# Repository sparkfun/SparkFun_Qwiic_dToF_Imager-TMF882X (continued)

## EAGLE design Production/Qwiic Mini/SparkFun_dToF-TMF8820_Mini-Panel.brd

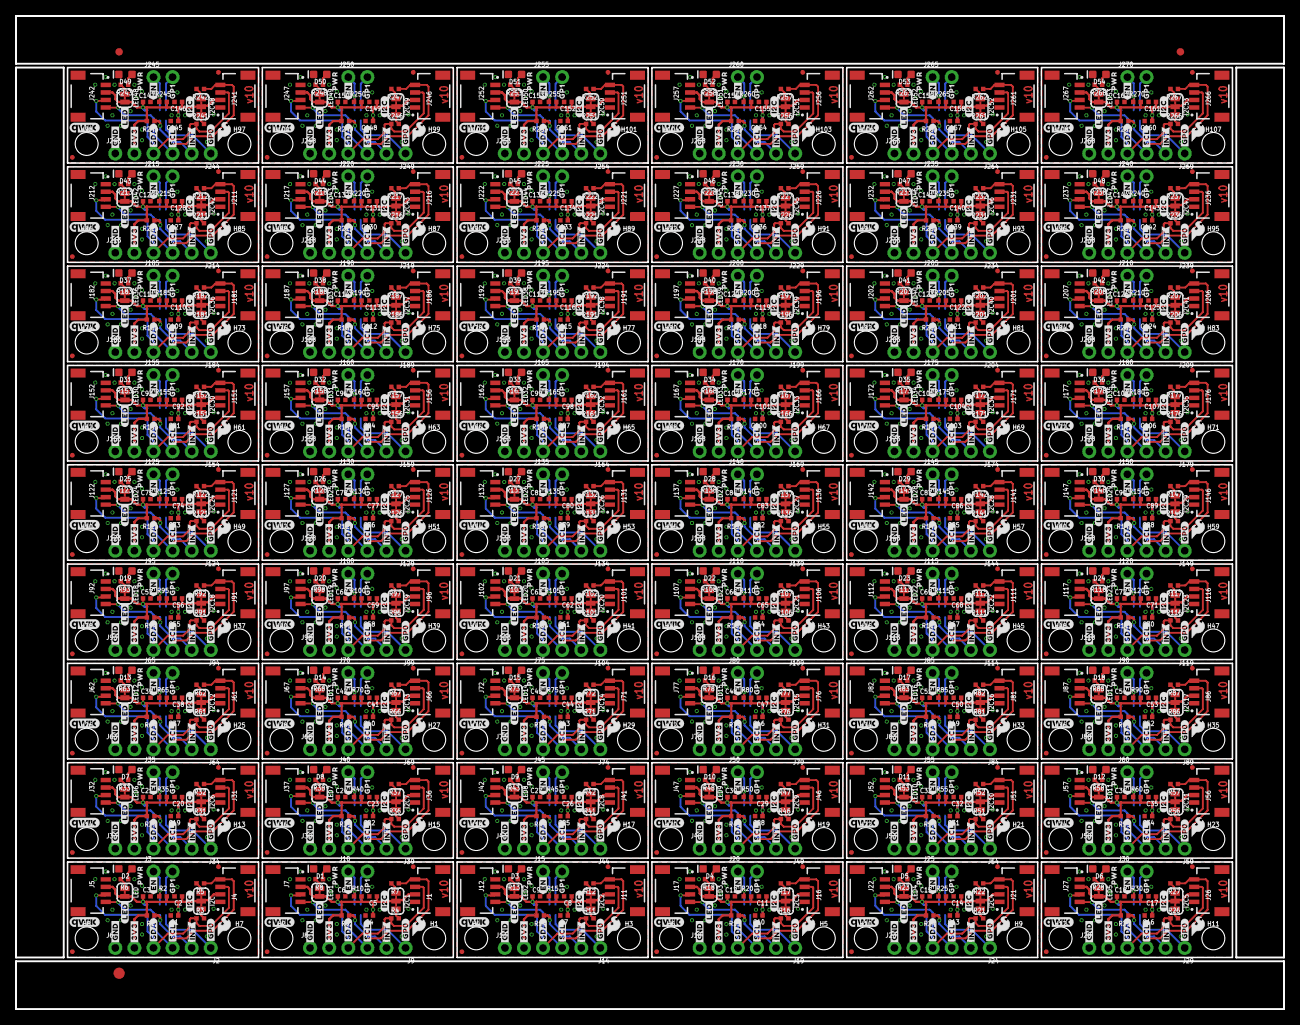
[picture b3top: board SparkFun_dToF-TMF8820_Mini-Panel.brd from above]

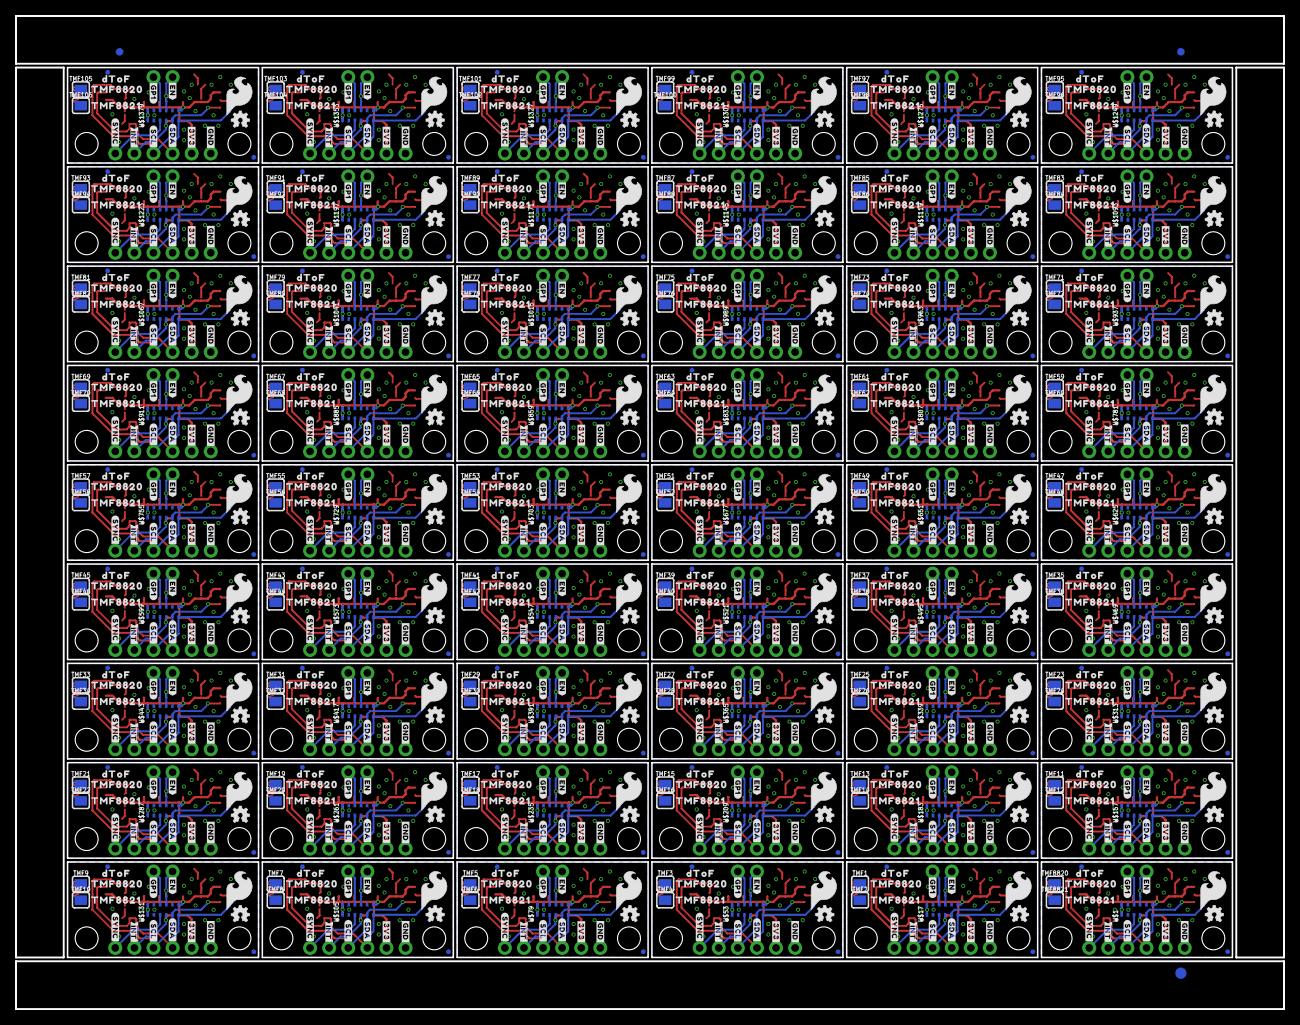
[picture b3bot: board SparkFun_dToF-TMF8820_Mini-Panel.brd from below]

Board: 2 copper layers, 168.7 x 132.1 mm, 2922 parts (975 on the bottom side), 648 nets.

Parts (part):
C1, C2, C3, C4, C5, C6, C7, C8, C9, C10, C11, C12, C13, C14, C15, C16, C17, C18, C19, C20, C21, C22, C23, C24, C25, C26, C27, C28, C29, C30, C31, C32, C33, C34, C35, C36, C37, C38, C39, C40, C41, C42, C43, C44, C45, C46, C47, C48, C49, C50, C51, C52, C53, C54, C55, C56, C57, C58, C59, C60, C61, C62, C63, C64, C65, C66, C67, C68, C69, C70, C71, C72, C73, C74, C75, C76, C77, C78, C79, C80, C81, C82, C83, C84, C85, C86, C87, C88, C89, C90, C91, C92, C93, C94, C95, C96, C97, C98, C99, C100, C101, C102, C103, C104, C105, C106, C107, C108, C109, C110, C111, C112, C113, C114, C115, C116, C117, C118, C119, C120, C121, C122, C123, C124, C125, C126, C127, C128, C129, C130, C131, C132, C133, C134, C135, C136, C137, C138, C139, C140, C141, C142, C143, C144, C145, C146, C147, C148, C149, C150, C151, C152, C153, C154, C155, C156, C157, C158, C159, C160, C161, C162: 0.1uF; 0402-TIGHT
D1, D2, D3, D4, D5, D6, D7, D8, D9, D10, D11, D12, D13, D14, D15, D16, D17, D18, D19, D20, D21, D22, D23, D24, D25, D26, D27, D28, D29, D30, D31, D32, D33, D34, D35, D36, D37, D38, D39, D40, D41, D42, D43, D44, D45, D46, D47, D48, D49, D50, D51, D52, D53, D54: RED; LED-0603
E$1, E$2, E$3, E$4: FIDUCIAL-1X2
E$5, E$6: FIDUCIAL-1.5X3
FD1, FD2, FD3, FD4, FD5, FD6, FD7, FD8, FD9, FD10, FD11, FD12, FD13, FD14, FD15, FD16, FD17, FD18, FD19, FD20, FD21, FD22, FD23, FD24, FD25, FD26, FD27, FD28, FD29, FD30, FD31, FD32, FD33, FD34, FD35, FD36, FD37, FD38, FD39, FD40, FD41, FD42, FD43, FD44, FD45, FD46, FD47, FD48, FD49, FD50, FD51, FD52, FD53, FD54, FD55, FD56, FD57, FD58, FD59, FD60, FD61, FD62, FD63, FD64, FD65, FD66, FD67, FD68, FD69, FD70, FD71, FD72, FD73, FD74, FD75, FD76, FD77, FD78, FD79, FD80, FD81, FD82, FD83, FD84, FD85, FD86, FD87, FD88, FD89, FD90, FD91, FD92, FD93, FD94, FD95, FD96, FD97, FD98, FD99, FD100, FD101, FD102, FD103, FD104, FD105, FD106, FD107, FD108, FD109, FD110, FD111, FD112, FD113, FD114, FD115, FD116, FD117, FD118, FD119, FD120, FD121, FD122, FD123, FD124, FD125, FD126, FD127, FD128, FD129, FD130, FD131, FD132, FD133, FD134, FD135, FD136, FD137, FD138, FD139, FD140, FD141, FD142, FD143, FD144, FD145, FD146, FD147, FD148, FD149, FD150, FD151, FD152, FD153, FD154, FD155, FD156, FD157, FD158, FD159, FD160, FD161, FD162, FD163, FD164, FD165, FD166, FD167, FD168, FD169, FD170, FD171, FD172, FD173, FD174, FD175, FD176, FD177, FD178, FD179, FD180, FD181, FD182, FD183, FD184, FD185, FD186, FD187, FD188, FD189, FD190, FD191, FD192, FD193, FD194, FD195, FD196, FD197, FD198, FD199, FD200, FD201, FD202, FD203, FD204, FD205, FD206, FD207, FD208, FD209, FD210, FD211, FD212, FD213, FD214, FD215, FD216: FIDUCIALUFIDUCIAL; FIDUCIAL-MICRO
FRAME1, FRAME2, FRAME3, FRAME4, FRAME5, FRAME6, FRAME7, FRAME8, FRAME9, FRAME10, FRAME11, FRAME12, FRAME13, FRAME14, FRAME15, FRAME16, FRAME17, FRAME18, FRAME19, FRAME20, FRAME21, FRAME22, FRAME23, FRAME24, FRAME25, FRAME26, FRAME27, FRAME28, FRAME29, FRAME30, FRAME31, FRAME32, FRAME33, FRAME34, FRAME35, FRAME36, FRAME37, FRAME38, FRAME39, FRAME40, FRAME41, FRAME42, FRAME43, FRAME44, FRAME45, FRAME46, FRAME47, FRAME48, FRAME49, FRAME50, FRAME51, FRAME52, FRAME53, FRAME54: FRAME-LETTER; CREATIVE_COMMONS
H1, H2, H3, H4, H5, H6, H7, H8, H9, H10, H11, H12, H13, H14, H15, H16, H17, H18, H19, H20, H21, H22, H23, H24, H25, H26, H27, H28, H29, H30, H31, H32, H33, H34, H35, H36, H37, H38, H39, H40, H41, H42, H43, H44, H45, H46, H47, H48, H49, H50, H51, H52, H53, H54, H55, H56, H57, H58, H59, H60, H61, H62, H63, H64, H65, H66, H67, H68, H69, H70, H71, H72, H73, H74, H75, H76, H77, H78, H79, H80, H81, H82, H83, H84, H85, H86, H87, H88, H89, H90, H91, H92, H93, H94, H95, H96, H97, H98, H99, H100, H101, H102, H103, H104, H105, H106, H107, H108: STAND-OFFTIGHT; STAND-OFF-TIGHT
I2C, I2C1, I2C2, I2C3, I2C4, I2C5, I2C6, I2C7, I2C8, I2C9, I2C10, I2C11, I2C12, I2C13, I2C14, I2C15, I2C16, I2C17, I2C18, I2C19, I2C20, I2C21, I2C22, I2C23, I2C24, I2C25, I2C26, I2C27, I2C28, I2C29, I2C30, I2C31, I2C32, I2C33, I2C34, I2C35, I2C36, I2C37, I2C38, I2C39, I2C40, I2C41, I2C42, I2C43, I2C44, I2C45, I2C46, I2C47, I2C48, I2C49, I2C50, I2C51, I2C52, I2C53: I2C_PU; SMT-JUMPER_3_2-NC_TRACE_SILK
J1, J4, J5, J7, J11, J12, J16, J17, J21, J22, J26, J27, J31, J32, J36, J37, J41, J42, J46, J47, J51, J52, J56, J57, J61, J62, J66, J67, J71, J72, J76, J77, J81, J82, J86, J87, J91, J92, J96, J97, J101, J102, J106, J107, J111, J112, J116, J117, J121, J122, J126, J127, J131, J132, J136, J137, J141, J142, J146, J147, J151, J152, J156, J157, J161, J162, J166, J167, J171, J172, J176, J177, J181, J182, J186, J187, J191, J192, J196, J197, J201, J202, J206, J207, J211, J212, J216, J217, J221, J222, J226, J227, J231, J232, J236, J237, J241, J242, J246, J247, J251, J252, J256, J257, J261, J262, J266, J267: QWIIC_RIGHT_ANGLE; JST04_1MM_RA
J2, J3, J9, J10, J14, J15, J19, J20, J24, J25, J29, J30, J34, J35, J39, J40, J44, J45, J49, J50, J54, J55, J59, J60, J64, J65, J69, J70, J74, J75, J79, J80, J84, J85, J89, J90, J94, J95, J99, J100, J104, J105, J109, J110, J114, J115, J119, J120, J124, J125, J129, J130, J134, J135, J139, J140, J144, J145, J149, J150, J154, J155, J159, J160, J164, J165, J169, J170, J174, J175, J179, J180, J184, J185, J189, J190, J194, J195, J199, J200, J204, J205, J209, J210, J214, J215, J219, J220, J224, J225, J229, J230, J234, J235, J239, J240, J244, J245, J249, J250, J254, J255, J259, J260, J264, J265, J269, J270: 1X02_NO_SILK
J6, J8, J13, J18, J23, J28, J33, J38, J43, J48, J53, J58, J63, J68, J73, J78, J83, J88, J93, J98, J103, J108, J113, J118, J123, J128, J133, J138, J143, J148, J153, J158, J163, J168, J173, J178, J183, J188, J193, J198, J203, J208, J213, J218, J223, J228, J233, J238, J243, J248, J253, J258, J263, J268: 1X04_NO_SILK
LED, LED1, LED2, LED3, LED4, LED5, LED6, LED7, LED8, LED9, LED10, LED11, LED12, LED13, LED14, LED15, LED16, LED17, LED18, LED19, LED20, LED21, LED22, LED23, LED24, LED25, LED26, LED27, LED28, LED29, LED30, LED31, LED32, LED33, LED34, LED35, LED36, LED37, LED38, LED39, LED40, LED41, LED42, LED43, LED44, LED45, LED46, LED47, LED48, LED49, LED50, LED51, LED52, LED53: LED; SMT-JUMPER_2_NC_TRACE_SILK
LOGO1, LOGO4, LOGO7, LOGO10, LOGO13, LOGO16, LOGO19, LOGO22, LOGO25, LOGO28, LOGO31, LOGO34, LOGO37, LOGO40, LOGO43, LOGO46, LOGO49, LOGO52, LOGO55, LOGO58, LOGO61, LOGO64, LOGO67, LOGO70, LOGO73, LOGO76, LOGO79, LOGO82, LOGO85, LOGO88, LOGO91, LOGO94, LOGO97, LOGO100, LOGO103, LOGO106, LOGO109, LOGO112, LOGO115, LOGO118, LOGO121, LOGO124, LOGO127, LOGO130, LOGO133, LOGO136, LOGO139, LOGO142, LOGO145, LOGO148, LOGO151, LOGO154, LOGO157, LOGO160: SFE_LOGO_NAMEBLANK; BLANK
LOGO2, LOGO5, LOGO8, LOGO11, LOGO14, LOGO17, LOGO20, LOGO23, LOGO26, LOGO29, LOGO32, LOGO35, LOGO38, LOGO41, LOGO44, LOGO47, LOGO50, LOGO53, LOGO56, LOGO59, LOGO62, LOGO65, LOGO68, LOGO71, LOGO74, LOGO77, LOGO80, LOGO83, LOGO86, LOGO89, LOGO92, LOGO95, LOGO98, LOGO101, LOGO104, LOGO107, LOGO110, LOGO113, LOGO116, LOGO119, LOGO122, LOGO125, LOGO128, LOGO131, LOGO134, LOGO137, LOGO140, LOGO143, LOGO146, LOGO149, LOGO152, LOGO155, LOGO158, LOGO161: QWIIC_LOGO_4MM; QWIIC_4MM
LOGO3, LOGO6, LOGO9, LOGO12, LOGO15, LOGO18, LOGO21, LOGO24, LOGO27, LOGO30, LOGO33, LOGO36, LOGO39, LOGO42, LOGO45, LOGO48, LOGO51, LOGO54, LOGO57, LOGO60, LOGO63, LOGO66, LOGO69, LOGO72, LOGO75, LOGO78, LOGO81, LOGO84, LOGO87, LOGO90, LOGO93, LOGO96, LOGO99, LOGO102, LOGO105, LOGO108, LOGO111, LOGO114, LOGO117, LOGO120, LOGO123, LOGO126, LOGO129, LOGO132, LOGO135, LOGO138, LOGO141, LOGO144, LOGO147, LOGO150, LOGO153, LOGO156, LOGO159, LOGO162: OSHW-LOGONO_SILK; DUMMY
R1, R2, R9, R10, R14, R15, R19, R20, R24, R25, R29, R30, R34, R35, R39, R40, R44, R45, R49, R50, R54, R55, R59, R60, R64, R65, R69, R70, R74, R75, R79, R80, R84, R85, R89, R90, R94, R95, R99, R100, R104, R105, R109, R110, R114, R115, R119, R120, R124, R125, R129, R130, R134, R135, R139, R140, R144, R145, R149, R150, R154, R155, R159, R160, R164, R165, R169, R170, R174, R175, R179, R180, R184, R185, R189, R190, R194, R195, R199, R200, R204, R205, R209, R210, R214, R215, R219, R220, R224, R225, R229, R230, R234, R235, R239, R240, R244, R245, R249, R250, R254, R255, R259, R260, R264, R265, R269, R270: 10k; 0402-TIGHT
R3, R4, R5, R7, R11, R12, R16, R17, R21, R22, R26, R27, R31, R32, R36, R37, R41, R42, R46, R47, R51, R52, R56, R57, R61, R62, R66, R67, R71, R72, R76, R77, R81, R82, R86, R87, R91, R92, R96, R97, R101, R102, R106, R107, R111, R112, R116, R117, R121, R122, R126, R127, R131, R132, R136, R137, R141, R142, R146, R147, R151, R152, R156, R157, R161, R162, R166, R167, R171, R172, R176, R177, R181, R182, R186, R187, R191, R192, R196, R197, R201, R202, R206, R207, R211, R212, R216, R217, R221, R222, R226, R227, R231, R232, R236, R237, R241, R242, R246, R247, R251, R252, R256, R257, R261, R262, R266, R267: 2.2k; 0402-TIGHT
R6, R8, R13, R18, R23, R28, R33, R38, R43, R48, R53, R58, R63, R68, R73, R78, R83, R88, R93, R98, R103, R108, R113, R118, R123, R128, R133, R138, R143, R148, R153, R158, R163, R168, R173, R178, R183, R188, R193, R198, R203, R208, R213, R218, R223, R228, R233, R238, R243, R248, R253, R258, R263, R268: 1k; 0402-TIGHT
TMF1, TMF3, TMF5, TMF7, TMF9, TMF11, TMF13, TMF15, TMF17, TMF19, TMF21, TMF23, TMF25, TMF27, TMF29, TMF31, TMF33, TMF35, TMF37, TMF39, TMF41, TMF43, TMF45, TMF47, TMF49, TMF51, TMF53, TMF55, TMF57, TMF59, TMF61, TMF63, TMF65, TMF67, TMF69, TMF71, TMF73, TMF75, TMF77, TMF79, TMF81, TMF83, TMF85, TMF87, TMF89, TMF91, TMF93, TMF95, TMF97, TMF99, TMF101, TMF103, TMF105, TMF8820: PROD_ID_PASTE_SILK; PRODUCT_IDENT_PASTE_SILK
TMF2, TMF4, TMF6, TMF8, TMF10, TMF12, TMF14, TMF16, TMF18, TMF20, TMF22, TMF24, TMF26, TMF28, TMF30, TMF32, TMF34, TMF36, TMF38, TMF40, TMF42, TMF44, TMF46, TMF48, TMF50, TMF52, TMF54, TMF56, TMF58, TMF60, TMF62, TMF64, TMF66, TMF68, TMF70, TMF72, TMF74, TMF76, TMF78, TMF80, TMF82, TMF84, TMF86, TMF88, TMF90, TMF92, TMF94, TMF96, TMF98, TMF100, TMF102, TMF104, TMF106, TMF8821: PROD_ID_NO-PASTE_SILK; PRODUCT_IDENT_NO_SILK
U$1, U$17, U$53, U$79, U$105, U$131, U$157, U$183, U$209, U$235, U$261, U$287, U$313, U$339, U$365, U$391, U$417, U$443, U$469, U$495, U$521, U$547, U$573, U$599, U$625, U$651, U$677, U$703, U$729, U$755, U$781, U$807, U$833, U$859, U$885, U$911, U$937, U$963, U$989, U$1015, U$1041, U$1067, U$1093, U$1119, U$1145, U$1171, U$1197, U$1223, U$1249, U$1275, U$1301, U$1327, U$1353, U$1379: TMF882X_TMF8820; TMF882X
U$2, U$49, U$75, U$101, U$127, U$153, U$179, U$205, U$231, U$257, U$283, U$309, U$335, U$361, U$387, U$413, U$439, U$465, U$491, U$517, U$543, U$569, U$595, U$621, U$647, U$673, U$699, U$725, U$751, U$777, U$803, U$829, U$855, U$881, U$907, U$933, U$959, U$985, U$1011, U$1037, U$1063, U$1089, U$1115, U$1141, U$1167, U$1193, U$1219, U$1245, U$1271, U$1297, U$1323, U$1349, U$1375, U$1401: #GP1#8
U$3, U$34, U$66, U$92, U$118, U$144, U$170, U$196, U$222, U$248, U$274, U$300, U$326, U$352, U$378, U$404, U$430, U$456, U$482, U$508, U$534, U$560, U$586, U$612, U$638, U$664, U$690, U$716, U$742, U$768, U$794, U$820, U$846, U$872, U$898, U$924, U$950, U$976, U$1002, U$1028, U$1054, U$1080, U$1106, U$1132, U$1158, U$1184, U$1210, U$1236, U$1262, U$1288, U$1314, U$1340, U$1366, U$1392: ##INT##9
U$4, U$36, U$67, U$93, U$119, U$145, U$171, U$197, U$223, U$249, U$275, U$301, U$327, U$353, U$379, U$405, U$431, U$457, U$483, U$509, U$535, U$561, U$587, U$613, U$639, U$665, U$691, U$717, U$743, U$769, U$795, U$821, U$847, U$873, U$899, U$925, U$951, U$977, U$1003, U$1029, U$1055, U$1081, U$1107, U$1133, U$1159, U$1185, U$1211, U$1237, U$1263, U$1289, U$1315, U$1341, U$1367, U$1393: ##INT##8
U$5, U$41, U$68, U$94, U$120, U$146, U$172, U$198, U$224, U$250, U$276, U$302, U$328, U$354, U$380, U$406, U$432, U$458, U$484, U$510, U$536, U$562, U$588, U$614, U$640, U$666, U$692, U$718, U$744, U$770, U$796, U$822, U$848, U$874, U$900, U$926, U$952, U$978, U$1004, U$1030, U$1056, U$1082, U$1108, U$1134, U$1160, U$1186, U$1212, U$1238, U$1264, U$1290, U$1316, U$1342, U$1368, U$1394: #SYNC#8
U$6, U$50, U$76, U$102, U$128, U$154, U$180, U$206, U$232, U$258, U$284, U$310, U$336, U$362, U$388, U$414, U$440, U$466, U$492, U$518, U$544, U$570, U$596, U$622, U$648, U$674, U$700, U$726, U$752, U$778, U$804, U$830, U$856, U$882, U$908, U$934, U$960, U$986, U$1012, U$1038, U$1064, U$1090, U$1116, U$1142, U$1168, U$1194, U$1220, U$1246, U$1272, U$1298, U$1324, U$1350, U$1376, U$1402: GP18
U$7, U$42, U$69, U$95, U$121, U$147, U$173, U$199, U$225, U$251, U$277, U$303, U$329, U$355, U$381, U$407, U$433, U$459, U$485, U$511, U$537, U$563, U$589, U$615, U$641, U$667, U$693, U$719, U$745, U$771, U$797, U$823, U$849, U$875, U$901, U$927, U$953, U$979, U$1005, U$1031, U$1057, U$1083, U$1109, U$1135, U$1161, U$1187, U$1213, U$1239, U$1265, U$1291, U$1317, U$1343, U$1369, U$1395: DTOF882188211
U$8, U$44, U$70, U$96, U$122, U$148, U$174, U$200, U$226, U$252, U$278, U$304, U$330, U$356, U$382, U$408, U$434, U$460, U$486, U$512, U$538, U$564, U$590, U$616, U$642, U$668, U$694, U$720, U$746, U$772, U$798, U$824, U$850, U$876, U$902, U$928, U$954, U$980, U$1006, U$1032, U$1058, U$1084, U$1110, U$1136, U$1162, U$1188, U$1214, U$1240, U$1266, U$1292, U$1318, U$1344, U$1370, U$1396: TMF88209
U$9, U$21, U$31, U$45, U$54, U$71, U$80, U$97, U$106, U$123, U$132, U$149, U$158, U$175, U$184, U$201, U$210, U$227, U$236, U$253, U$262, U$279, U$288, U$305, U$314, U$331, U$340, U$357, U$366, U$383, U$392, U$409, U$418, U$435, U$444, U$461, U$470, U$487, U$496, U$513, U$522, U$539, U$548, U$565, U$574, U$591, U$600, U$617, U$626, U$643, U$652, U$669, U$678, U$695, U$704, U$721, U$730, U$747, U$756, U$773, U$782, U$799, U$808, U$825, U$834, U$851, U$860, U$877, U$886, U$903, U$912, U$929, U$938, U$955, U$964, U$981, U$990, U$1007, U$1016, U$1033, U$1042, U$1059, U$1068, U$1085, U$1094, U$1111, U$1120, U$1137, U$1146, U$1163, U$1172, U$1189, U$1198, U$1215, U$1224, U$1241, U$1250, U$1267, U$1276, U$1293, U$1302, U$1319, U$1328, U$1345, U$1354, U$1371, U$1380, U$1397: #EN#7
U$10, U$22, U$28, U$37, U$55, U$61, U$81, U$87, U$107, U$113, U$133, U$139, U$159, U$165, U$185, U$191, U$211, U$217, U$237, U$243, U$263, U$269, U$289, U$295, U$315, U$321, U$341, U$347, U$367, U$373, U$393, U$399, U$419, U$425, U$445, U$451, U$471, U$477, U$497, U$503, U$523, U$529, U$549, U$555, U$575, U$581, U$601, U$607, U$627, U$633, U$653, U$659, U$679, U$685, U$705, U$711, U$731, U$737, U$757, U$763, U$783, U$789, U$809, U$815, U$835, U$841, U$861, U$867, U$887, U$893, U$913, U$919, U$939, U$945, U$965, U$971, U$991, U$997, U$1017, U$1023, U$1043, U$1049, U$1069, U$1075, U$1095, U$1101, U$1121, U$1127, U$1147, U$1153, U$1173, U$1179, U$1199, U$1205, U$1225, U$1231, U$1251, U$1257, U$1277, U$1283, U$1303, U$1309, U$1329, U$1335, U$1355, U$1361, U$1381, U$1387: #3V3#0
U$11, U$46, U$72, U$98, U$124, U$150, U$176, U$202, U$228, U$254, U$280, U$306, U$332, U$358, U$384, U$410, U$436, U$462, U$488, U$514, U$540, U$566, U$592, U$618, U$644, U$670, U$696, U$722, U$748, U$774, U$800, U$826, U$852, U$878, U$904, U$930, U$956, U$982, U$1008, U$1034, U$1060, U$1086, U$1112, U$1138, U$1164, U$1190, U$1216, U$1242, U$1268, U$1294, U$1320, U$1346, U$1372, U$1398: TMF882188210
U$12, U$51, U$77, U$103, U$129, U$155, U$181, U$207, U$233, U$259, U$285, U$311, U$337, U$363, U$389, U$415, U$441, U$467, U$493, U$519, U$545, U$571, U$597, U$623, U$649, U$675, U$701, U$727, U$753, U$779, U$805, U$831, U$857, U$883, U$909, U$935, U$961, U$987, U$1013, U$1039, U$1065, U$1091, U$1117, U$1143, U$1169, U$1195, U$1221, U$1247, U$1273, U$1299, U$1325, U$1351, U$1377, U$1403: SFE_LOGO_FLAME_.2
U$13, U$47, U$73, U$99, U$125, U$151, U$177, U$203, U$229, U$255, U$281, U$307, U$333, U$359, U$385, U$411, U$437, U$463, U$489, U$515, U$541, U$567, U$593, U$619, U$645, U$671, U$697, U$723, U$749, U$775, U$801, U$827, U$853, U$879, U$905, U$931, U$957, U$983, U$1009, U$1035, U$1061, U$1087, U$1113, U$1139, U$1165, U$1191, U$1217, U$1243, U$1269, U$1295, U$1321, U$1347, U$1373, U$1399: #LED#10
U$14, U$48, U$74, U$100, U$126, U$152, U$178, U$204, U$230, U$256, U$282, U$308, U$334, U$360, U$386, U$412, U$438, U$464, U$490, U$516, U$542, U$568, U$594, U$620, U$646, U$672, U$698, U$724, U$750, U$776, U$802, U$828, U$854, U$880, U$906, U$932, U$958, U$984, U$1010, U$1036, U$1062, U$1088, U$1114, U$1140, U$1166, U$1192, U$1218, U$1244, U$1270, U$1296, U$1322, U$1348, U$1374, U$1400: #GP0#19
U$15, U$52, U$78, U$104, U$130, U$156, U$182, U$208, U$234, U$260, U$286, U$312, U$338, U$364, U$390, U$416, U$442, U$468, U$494, U$520, U$546, U$572, U$598, U$624, U$650, U$676, U$702, U$728, U$754, U$780, U$806, U$832, U$858, U$884, U$910, U$936, U$962, U$988, U$1014, U$1040, U$1066, U$1092, U$1118, U$1144, U$1170, U$1196, U$1222, U$1248, U$1274, U$1300, U$1326, U$1352, U$1378, U$1404: OSHW-LOGO-MINI
U$16, U$23, U$29, U$38, U$56, U$62, U$82, U$88, U$108, U$114, U$134, U$140, U$160, U$166, U$186, U$192, U$212, U$218, U$238, U$244, U$264, U$270, U$290, U$296, U$316, U$322, U$342, U$348, U$368, U$374, U$394, U$400, U$420, U$426, U$446, U$452, U$472, U$478, U$498, U$504, U$524, U$530, U$550, U$556, U$576, U$582, U$602, U$608, U$628, U$634, U$654, U$660, U$680, U$686, U$706, U$712, U$732, U$738, U$758, U$764, U$784, U$790, U$810, U$816, U$836, U$842, U$862, U$868, U$888, U$894, U$914, U$920, U$940, U$946, U$966, U$972, U$992, U$998, U$1018, U$1024, U$1044, U$1050, U$1070, U$1076, U$1096, U$1102, U$1122, U$1128, U$1148, U$1154, U$1174, U$1180, U$1200, U$1206, U$1226, U$1232, U$1252, U$1258, U$1278, U$1284, U$1304, U$1310, U$1330, U$1336, U$1356, U$1362, U$1382, U$1388: #GND#4
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
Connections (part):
3.3V: C1.1, C2.1, C3.1, I2C.2, J4.2, J5.2, J6.2, LED.2, R1.2, R2.2, U$1.P1, U$1.P7, U$1.P12
3.3V1: C4.1, C5.1, C6.1, I2C1.2, J1.2, J7.2, J8.2, LED1.2, R9.2, R10.2, U$17.P1, U$17.P7, U$17.P12
3.3V2: C7.1, C8.1, C9.1, I2C2.2, J11.2, J12.2, J13.2, LED2.2, R14.2, R15.2, U$53.P1, U$53.P7, U$53.P12
3.3V3: C10.1, C11.1, C12.1, I2C3.2, J16.2, J17.2, J18.2, LED3.2, R19.2, R20.2, U$79.P1, U$79.P7, U$79.P12
3.3V4: C13.1, C14.1, C15.1, I2C4.2, J21.2, J22.2, J23.2, LED4.2, R24.2, R25.2, U$105.P1, U$105.P7, U$105.P12
3.3V5: C16.1, C17.1, C18.1, I2C5.2, J26.2, J27.2, J28.2, LED5.2, R29.2, R30.2, U$131.P1, U$131.P7, U$131.P12
3.3V6: C19.1, C20.1, C21.1, I2C6.2, J31.2, J32.2, J33.2, LED6.2, R34.2, R35.2, U$157.P1, U$157.P7, U$157.P12
3.3V7: C22.1, C23.1, C24.1, I2C7.2, J36.2, J37.2, J38.2, LED7.2, R39.2, R40.2, U$183.P1, U$183.P7, U$183.P12
3.3V8: C25.1, C26.1, C27.1, I2C8.2, J41.2, J42.2, J43.2, LED8.2, R44.2, R45.2, U$209.P1, U$209.P7, U$209.P12
3.3V9: C28.1, C29.1, C30.1, I2C9.2, J46.2, J47.2, J48.2, LED9.2, R49.2, R50.2, U$235.P1, U$235.P7, U$235.P12
3.3V10: C31.1, C32.1, C33.1, I2C10.2, J51.2, J52.2, J53.2, LED10.2, R54.2, R55.2, U$261.P1, U$261.P7, U$261.P12
3.3V11: C34.1, C35.1, C36.1, I2C11.2, J56.2, J57.2, J58.2, LED11.2, R59.2, R60.2, U$287.P1, U$287.P7, U$287.P12
3.3V12: C37.1, C38.1, C39.1, I2C12.2, J61.2, J62.2, J63.2, LED12.2, R64.2, R65.2, U$313.P1, U$313.P7, U$313.P12
3.3V13: C40.1, C41.1, C42.1, I2C13.2, J66.2, J67.2, J68.2, LED13.2, R69.2, R70.2, U$339.P1, U$339.P7, U$339.P12
3.3V14: C43.1, C44.1, C45.1, I2C14.2, J71.2, J72.2, J73.2, LED14.2, R74.2, R75.2, U$365.P1, U$365.P7, U$365.P12
3.3V15: C46.1, C47.1, C48.1, I2C15.2, J76.2, J77.2, J78.2, LED15.2, R79.2, R80.2, U$391.P1, U$391.P7, U$391.P12
3.3V16: C49.1, C50.1, C51.1, I2C16.2, J81.2, J82.2, J83.2, LED16.2, R84.2, R85.2, U$417.P1, U$417.P7, U$417.P12
3.3V17: C52.1, C53.1, C54.1, I2C17.2, J86.2, J87.2, J88.2, LED17.2, R89.2, R90.2, U$443.P1, U$443.P7, U$443.P12
3.3V18: C55.1, C56.1, C57.1, I2C18.2, J91.2, J92.2, J93.2, LED18.2, R94.2, R95.2, U$469.P1, U$469.P7, U$469.P12
3.3V19: C58.1, C59.1, C60.1, I2C19.2, J96.2, J97.2, J98.2, LED19.2, R99.2, R100.2, U$495.P1, U$495.P7, U$495.P12
3.3V20: C61.1, C62.1, C63.1, I2C20.2, J101.2, J102.2, J103.2, LED20.2, R104.2, R105.2, U$521.P1, U$521.P7, U$521.P12
3.3V21: C64.1, C65.1, C66.1, I2C21.2, J106.2, J107.2, J108.2, LED21.2, R109.2, R110.2, U$547.P1, U$547.P7, U$547.P12
3.3V22: C67.1, C68.1, C69.1, I2C22.2, J111.2, J112.2, J113.2, LED22.2, R114.2, R115.2, U$573.P1, U$573.P7, U$573.P12
3.3V23: C70.1, C71.1, C72.1, I2C23.2, J116.2, J117.2, J118.2, LED23.2, R119.2, R120.2, U$599.P1, U$599.P7, U$599.P12
3.3V24: C73.1, C74.1, C75.1, I2C24.2, J121.2, J122.2, J123.2, LED24.2, R124.2, R125.2, U$625.P1, U$625.P7, U$625.P12
3.3V25: C76.1, C77.1, C78.1, I2C25.2, J126.2, J127.2, J128.2, LED25.2, R129.2, R130.2, U$651.P1, U$651.P7, U$651.P12
3.3V26: C79.1, C80.1, C81.1, I2C26.2, J131.2, J132.2, J133.2, LED26.2, R134.2, R135.2, U$677.P1, U$677.P7, U$677.P12
3.3V27: C82.1, C83.1, C84.1, I2C27.2, J136.2, J137.2, J138.2, LED27.2, R139.2, R140.2, U$703.P1, U$703.P7, U$703.P12
3.3V28: C85.1, C86.1, C87.1, I2C28.2, J141.2, J142.2, J143.2, LED28.2, R144.2, R145.2, U$729.P1, U$729.P7, U$729.P12
3.3V29: C88.1, C89.1, C90.1, I2C29.2, J146.2, J147.2, J148.2, LED29.2, R149.2, R150.2, U$755.P1, U$755.P7, U$755.P12
3.3V30: C91.1, C92.1, C93.1, I2C30.2, J151.2, J152.2, J153.2, LED30.2, R154.2, R155.2, U$781.P1, U$781.P7, U$781.P12
3.3V31: C94.1, C95.1, C96.1, I2C31.2, J156.2, J157.2, J158.2, LED31.2, R159.2, R160.2, U$807.P1, U$807.P7, U$807.P12
3.3V32: C97.1, C98.1, C99.1, I2C32.2, J161.2, J162.2, J163.2, LED32.2, R164.2, R165.2, U$833.P1, U$833.P7, U$833.P12
3.3V33: C100.1, C101.1, C102.1, I2C33.2, J166.2, J167.2, J168.2, LED33.2, R169.2, R170.2, U$859.P1, U$859.P7, U$859.P12
3.3V34: C103.1, C104.1, C105.1, I2C34.2, J171.2, J172.2, J173.2, LED34.2, R174.2, R175.2, U$885.P1, U$885.P7, U$885.P12
3.3V35: C106.1, C107.1, C108.1, I2C35.2, J176.2, J177.2, J178.2, LED35.2, R179.2, R180.2, U$911.P1, U$911.P7, U$911.P12
3.3V36: C109.1, C110.1, C111.1, I2C36.2, J181.2, J182.2, J183.2, LED36.2, R184.2, R185.2, U$937.P1, U$937.P7, U$937.P12
3.3V37: C112.1, C113.1, C114.1, I2C37.2, J186.2, J187.2, J188.2, LED37.2, R189.2, R190.2, U$963.P1, U$963.P7, U$963.P12
3.3V38: C115.1, C116.1, C117.1, I2C38.2, J191.2, J192.2, J193.2, LED38.2, R194.2, R195.2, U$989.P1, U$989.P7, U$989.P12
3.3V39: C118.1, C119.1, C120.1, I2C39.2, J196.2, J197.2, J198.2, LED39.2, R199.2, R200.2, U$1015.P1, U$1015.P7, U$1015.P12
3.3V40: C121.1, C122.1, C123.1, I2C40.2, J201.2, J202.2, J203.2, LED40.2, R204.2, R205.2, U$1041.P1, U$1041.P7, U$1041.P12
3.3V41: C124.1, C125.1, C126.1, I2C41.2, J206.2, J207.2, J208.2, LED41.2, R209.2, R210.2, U$1067.P1, U$1067.P7, U$1067.P12
3.3V42: C127.1, C128.1, C129.1, I2C42.2, J211.2, J212.2, J213.2, LED42.2, R214.2, R215.2, U$1093.P1, U$1093.P7, U$1093.P12
3.3V43: C130.1, C131.1, C132.1, I2C43.2, J216.2, J217.2, J218.2, LED43.2, R219.2, R220.2, U$1119.P1, U$1119.P7, U$1119.P12
3.3V44: C133.1, C134.1, C135.1, I2C44.2, J221.2, J222.2, J223.2, LED44.2, R224.2, R225.2, U$1145.P1, U$1145.P7, U$1145.P12
3.3V45: C136.1, C137.1, C138.1, I2C45.2, J226.2, J227.2, J228.2, LED45.2, R229.2, R230.2, U$1171.P1, U$1171.P7, U$1171.P12
3.3V46: C139.1, C140.1, C141.1, I2C46.2, J231.2, J232.2, J233.2, LED46.2, R234.2, R235.2, U$1197.P1, U$1197.P7, U$1197.P12
3.3V47: C142.1, C143.1, C144.1, I2C47.2, J236.2, J237.2, J238.2, LED47.2, R239.2, R240.2, U$1223.P1, U$1223.P7, U$1223.P12
3.3V48: C145.1, C146.1, C147.1, I2C48.2, J241.2, J242.2, J243.2, LED48.2, R244.2, R245.2, U$1249.P1, U$1249.P7, U$1249.P12
3.3V49: C148.1, C149.1, C150.1, I2C49.2, J246.2, J247.2, J248.2, LED49.2, R249.2, R250.2, U$1275.P1, U$1275.P7, U$1275.P12
3.3V50: C151.1, C152.1, C153.1, I2C50.2, J251.2, J252.2, J253.2, LED50.2, R254.2, R255.2, U$1301.P1, U$1301.P7, U$1301.P12
3.3V51: C154.1, C155.1, C156.1, I2C51.2, J256.2, J257.2, J258.2, LED51.2, R259.2, R260.2, U$1327.P1, U$1327.P7, U$1327.P12
3.3V52: C157.1, C158.1, C159.1, I2C52.2, J261.2, J262.2, J263.2, LED52.2, R264.2, R265.2, U$1353.P1, U$1353.P7, U$1353.P12
3.3V53: C160.1, C161.1, C162.1, I2C53.2, J266.2, J267.2, J268.2, LED53.2, R269.2, R270.2, U$1379.P1, U$1379.P7, U$1379.P12
!INT!: J2.2, R1.1, U$1.P4
!INT!1: J9.2, R9.1, U$17.P4
!INT!2: J14.2, R14.1, U$53.P4
!INT!3: J19.2, R19.1, U$79.P4
!INT!4: J24.2, R24.1, U$105.P4
!INT!5: J29.2, R29.1, U$131.P4
!INT!6: J34.2, R34.1, U$157.P4
!INT!7: J39.2, R39.1, U$183.P4
!INT!8: J44.2, R44.1, U$209.P4
!INT!9: J49.2, R49.1, U$235.P4
!INT!10: J54.2, R54.1, U$261.P4
!INT!11: J59.2, R59.1, U$287.P4
!INT!12: J64.2, R64.1, U$313.P4
!INT!13: J69.2, R69.1, U$339.P4
!INT!14: J74.2, R74.1, U$365.P4
!INT!15: J79.2, R79.1, U$391.P4
!INT!16: J84.2, R84.1, U$417.P4
!INT!17: J89.2, R89.1, U$443.P4
!INT!18: J94.2, R94.1, U$469.P4
!INT!19: J99.2, R99.1, U$495.P4
!INT!20: J104.2, R104.1, U$521.P4
!INT!21: J109.2, R109.1, U$547.P4
!INT!22: J114.2, R114.1, U$573.P4
!INT!23: J119.2, R119.1, U$599.P4
!INT!24: J124.2, R124.1, U$625.P4
!INT!25: J129.2, R129.1, U$651.P4
!INT!26: J134.2, R134.1, U$677.P4
!INT!27: J139.2, R139.1, U$703.P4
!INT!28: J144.2, R144.1, U$729.P4
!INT!29: J149.2, R149.1, U$755.P4
!INT!30: J154.2, R154.1, U$781.P4
!INT!31: J159.2, R159.1, U$807.P4
!INT!32: J164.2, R164.1, U$833.P4
!INT!33: J169.2, R169.1, U$859.P4
!INT!34: J174.2, R174.1, U$885.P4
!INT!35: J179.2, R179.1, U$911.P4
!INT!36: J184.2, R184.1, U$937.P4
!INT!37: J189.2, R189.1, U$963.P4
!INT!38: J194.2, R194.1, U$989.P4
!INT!39: J199.2, R199.1, U$1015.P4
!INT!40: J204.2, R204.1, U$1041.P4
!INT!41: J209.2, R209.1, U$1067.P4
!INT!42: J214.2, R214.1, U$1093.P4
!INT!43: J219.2, R219.1, U$1119.P4
!INT!44: J224.2, R224.1, U$1145.P4
!INT!45: J229.2, R229.1, U$1171.P4
!INT!46: J234.2, R234.1, U$1197.P4
!INT!47: J239.2, R239.1, U$1223.P4
!INT!48: J244.2, R244.1, U$1249.P4
!INT!49: J249.2, R249.1, U$1275.P4
!INT!50: J254.2, R254.1, U$1301.P4
!INT!51: J259.2, R259.1, U$1327.P4
!INT!52: J264.2, R264.1, U$1353.P4
!INT!53: J269.2, R269.1, U$1379.P4
EN: J3.1, R2.1, U$1.P9
EN1: J10.1, R10.1, U$17.P9
EN2: J15.1, R15.1, U$53.P9
EN3: J20.1, R20.1, U$79.P9
EN4: J25.1, R25.1, U$105.P9
EN5: J30.1, R30.1, U$131.P9
EN6: J35.1, R35.1, U$157.P9
EN7: J40.1, R40.1, U$183.P9
EN8: J45.1, R45.1, U$209.P9
EN9: J50.1, R50.1, U$235.P9
EN10: J55.1, R55.1, U$261.P9
EN11: J60.1, R60.1, U$287.P9
EN12: J65.1, R65.1, U$313.P9
EN13: J70.1, R70.1, U$339.P9
EN14: J75.1, R75.1, U$365.P9
EN15: J80.1, R80.1, U$391.P9
EN16: J85.1, R85.1, U$417.P9
EN17: J90.1, R90.1, U$443.P9
EN18: J95.1, R95.1, U$469.P9
EN19: J100.1, R100.1, U$495.P9
EN20: J105.1, R105.1, U$521.P9
EN21: J110.1, R110.1, U$547.P9
EN22: J115.1, R115.1, U$573.P9
EN23: J120.1, R120.1, U$599.P9
EN24: J125.1, R125.1, U$625.P9
EN25: J130.1, R130.1, U$651.P9
EN26: J135.1, R135.1, U$677.P9
EN27: J140.1, R140.1, U$703.P9
EN28: J145.1, R145.1, U$729.P9
EN29: J150.1, R150.1, U$755.P9
EN30: J155.1, R155.1, U$781.P9
EN31: J160.1, R160.1, U$807.P9
EN32: J165.1, R165.1, U$833.P9
EN33: J170.1, R170.1, U$859.P9
EN34: J175.1, R175.1, U$885.P9
EN35: J180.1, R180.1, U$911.P9
EN36: J185.1, R185.1, U$937.P9
EN37: J190.1, R190.1, U$963.P9
EN38: J195.1, R195.1, U$989.P9
EN39: J200.1, R200.1, U$1015.P9
EN40: J205.1, R205.1, U$1041.P9
EN41: J210.1, R210.1, U$1067.P9
EN42: J215.1, R215.1, U$1093.P9
EN43: J220.1, R220.1, U$1119.P9
EN44: J225.1, R225.1, U$1145.P9
EN45: J230.1, R230.1, U$1171.P9
EN46: J235.1, R235.1, U$1197.P9
EN47: J240.1, R240.1, U$1223.P9
EN48: J245.1, R245.1, U$1249.P9
EN49: J250.1, R250.1, U$1275.P9
EN50: J255.1, R255.1, U$1301.P9
EN51: J260.1, R260.1, U$1327.P9
EN52: J265.1, R265.1, U$1353.P9
EN53: J270.1, R270.1, U$1379.P9
GND: C1.2, C2.2, C3.2, D2.C, J4.1, J5.1, J6.1, U$1.P2, U$1.P8, U$1.P11
GND1: C4.2, C5.2, C6.2, D1.C, J1.1, J7.1, J8.1, U$17.P2, U$17.P8, U$17.P11
GND2: C7.2, C8.2, C9.2, D3.C, J11.1, J12.1, J13.1, U$53.P2, U$53.P8, U$53.P11
GND3: C10.2, C11.2, C12.2, D4.C, J16.1, J17.1, J18.1, U$79.P2, U$79.P8, U$79.P11
GND4: C13.2, C14.2, C15.2, D5.C, J21.1, J22.1, J23.1, U$105.P2, U$105.P8, U$105.P11
GND5: C16.2, C17.2, C18.2, D6.C, J26.1, J27.1, J28.1, U$131.P2, U$131.P8, U$131.P11
GND6: C19.2, C20.2, C21.2, D7.C, J31.1, J32.1, J33.1, U$157.P2, U$157.P8, U$157.P11
GND7: C22.2, C23.2, C24.2, D8.C, J36.1, J37.1, J38.1, U$183.P2, U$183.P8, U$183.P11
GND8: C25.2, C26.2, C27.2, D9.C, J41.1, J42.1, J43.1, U$209.P2, U$209.P8, U$209.P11
GND9: C28.2, C29.2, C30.2, D10.C, J46.1, J47.1, J48.1, U$235.P2, U$235.P8, U$235.P11
GND10: C31.2, C32.2, C33.2, D11.C, J51.1, J52.1, J53.1, U$261.P2, U$261.P8, U$261.P11
GND11: C34.2, C35.2, C36.2, D12.C, J56.1, J57.1, J58.1, U$287.P2, U$287.P8, U$287.P11
GND12: C37.2, C38.2, C39.2, D13.C, J61.1, J62.1, J63.1, U$313.P2, U$313.P8, U$313.P11
GND13: C40.2, C41.2, C42.2, D14.C, J66.1, J67.1, J68.1, U$339.P2, U$339.P8, U$339.P11
GND14: C43.2, C44.2, C45.2, D15.C, J71.1, J72.1, J73.1, U$365.P2, U$365.P8, U$365.P11
GND15: C46.2, C47.2, C48.2, D16.C, J76.1, J77.1, J78.1, U$391.P2, U$391.P8, U$391.P11
GND16: C49.2, C50.2, C51.2, D17.C, J81.1, J82.1, J83.1, U$417.P2, U$417.P8, U$417.P11
GND17: C52.2, C53.2, C54.2, D18.C, J86.1, J87.1, J88.1, U$443.P2, U$443.P8, U$443.P11
GND18: C55.2, C56.2, C57.2, D19.C, J91.1, J92.1, J93.1, U$469.P2, U$469.P8, U$469.P11
GND19: C58.2, C59.2, C60.2, D20.C, J96.1, J97.1, J98.1, U$495.P2, U$495.P8, U$495.P11
GND20: C61.2, C62.2, C63.2, D21.C, J101.1, J102.1, J103.1, U$521.P2, U$521.P8, U$521.P11
GND21: C64.2, C65.2, C66.2, D22.C, J106.1, J107.1, J108.1, U$547.P2, U$547.P8, U$547.P11
GND22: C67.2, C68.2, C69.2, D23.C, J111.1, J112.1, J113.1, U$573.P2, U$573.P8, U$573.P11
GND23: C70.2, C71.2, C72.2, D24.C, J116.1, J117.1, J118.1, U$599.P2, U$599.P8, U$599.P11
GND24: C73.2, C74.2, C75.2, D25.C, J121.1, J122.1, J123.1, U$625.P2, U$625.P8, U$625.P11
GND25: C76.2, C77.2, C78.2, D26.C, J126.1, J127.1, J128.1, U$651.P2, U$651.P8, U$651.P11
GND26: C79.2, C80.2, C81.2, D27.C, J131.1, J132.1, J133.1, U$677.P2, U$677.P8, U$677.P11
GND27: C82.2, C83.2, C84.2, D28.C, J136.1, J137.1, J138.1, U$703.P2, U$703.P8, U$703.P11
GND28: C85.2, C86.2, C87.2, D29.C, J141.1, J142.1, J143.1, U$729.P2, U$729.P8, U$729.P11
GND29: C88.2, C89.2, C90.2, D30.C, J146.1, J147.1, J148.1, U$755.P2, U$755.P8, U$755.P11
GND30: C91.2, C92.2, C93.2, D31.C, J151.1, J152.1, J153.1, U$781.P2, U$781.P8, U$781.P11
GND31: C94.2, C95.2, C96.2, D32.C, J156.1, J157.1, J158.1, U$807.P2, U$807.P8, U$807.P11
GND32: C97.2, C98.2, C99.2, D33.C, J161.1, J162.1, J163.1, U$833.P2, U$833.P8, U$833.P11
GND33: C100.2, C101.2, C102.2, D34.C, J166.1, J167.1, J168.1, U$859.P2, U$859.P8, U$859.P11
GND34: C103.2, C104.2, C105.2, D35.C, J171.1, J172.1, J173.1, U$885.P2, U$885.P8, U$885.P11
GND35: C106.2, C107.2, C108.2, D36.C, J176.1, J177.1, J178.1, U$911.P2, U$911.P8, U$911.P11
GND36: C109.2, C110.2, C111.2, D37.C, J181.1, J182.1, J183.1, U$937.P2, U$937.P8, U$937.P11
GND37: C112.2, C113.2, C114.2, D38.C, J186.1, J187.1, J188.1, U$963.P2, U$963.P8, U$963.P11
GND38: C115.2, C116.2, C117.2, D39.C, J191.1, J192.1, J193.1, U$989.P2, U$989.P8, U$989.P11
GND39: C118.2, C119.2, C120.2, D40.C, J196.1, J197.1, J198.1, U$1015.P2, U$1015.P8, U$1015.P11
GND40: C121.2, C122.2, C123.2, D41.C, J201.1, J202.1, J203.1, U$1041.P2, U$1041.P8, U$1041.P11
GND41: C124.2, C125.2, C126.2, D42.C, J206.1, J207.1, J208.1, U$1067.P2, U$1067.P8, U$1067.P11
GND42: C127.2, C128.2, C129.2, D43.C, J211.1, J212.1, J213.1, U$1093.P2, U$1093.P8, U$1093.P11
GND43: C130.2, C131.2, C132.2, D44.C, J216.1, J217.1, J218.1, U$1119.P2, U$1119.P8, U$1119.P11
GND44: C133.2, C134.2, C135.2, D45.C, J221.1, J222.1, J223.1, U$1145.P2, U$1145.P8, U$1145.P11
GND45: C136.2, C137.2, C138.2, D46.C, J226.1, J227.1, J228.1, U$1171.P2, U$1171.P8, U$1171.P11
GND46: C139.2, C140.2, C141.2, D47.C, J231.1, J232.1, J233.1, U$1197.P2, U$1197.P8, U$1197.P11
GND47: C142.2, C143.2, C144.2, D48.C, J236.1, J237.1, J238.1, U$1223.P2, U$1223.P8, U$1223.P11
GND48: C145.2, C146.2, C147.2, D49.C, J241.1, J242.1, J243.1, U$1249.P2, U$1249.P8, U$1249.P11
GND49: C148.2, C149.2, C150.2, D50.C, J246.1, J247.1, J248.1, U$1275.P2, U$1275.P8, U$1275.P11
GND50: C151.2, C152.2, C153.2, D51.C, J251.1, J252.1, J253.1, U$1301.P2, U$1301.P8, U$1301.P11
GND51: C154.2, C155.2, C156.2, D52.C, J256.1, J257.1, J258.1, U$1327.P2, U$1327.P8, U$1327.P11
GND52: C157.2, C158.2, C159.2, D53.C, J261.1, J262.1, J263.1, U$1353.P2, U$1353.P8, U$1353.P11
GND53: C160.2, C161.2, C162.2, D54.C, J266.1, J267.1, J268.1, U$1379.P2, U$1379.P8, U$1379.P11
GPIO0/SYNC: J2.1, U$1.P3
GPIO0/SYNC1: J9.1, U$17.P3
GPIO0/SYNC2: J14.1, U$53.P3
GPIO0/SYNC3: J19.1, U$79.P3
GPIO0/SYNC4: J24.1, U$105.P3
GPIO0/SYNC5: J29.1, U$131.P3
GPIO0/SYNC6: J34.1, U$157.P3
GPIO0/SYNC7: J39.1, U$183.P3
GPIO0/SYNC8: J44.1, U$209.P3
GPIO0/SYNC9: J49.1, U$235.P3
GPIO0/SYNC10: J54.1, U$261.P3
GPIO0/SYNC11: J59.1, U$287.P3
GPIO0/SYNC12: J64.1, U$313.P3
GPIO0/SYNC13: J69.1, U$339.P3
GPIO0/SYNC14: J74.1, U$365.P3
GPIO0/SYNC15: J79.1, U$391.P3
GPIO0/SYNC16: J84.1, U$417.P3
GPIO0/SYNC17: J89.1, U$443.P3
GPIO0/SYNC18: J94.1, U$469.P3
GPIO0/SYNC19: J99.1, U$495.P3
GPIO0/SYNC20: J104.1, U$521.P3
GPIO0/SYNC21: J109.1, U$547.P3
GPIO0/SYNC22: J114.1, U$573.P3
GPIO0/SYNC23: J119.1, U$599.P3
GPIO0/SYNC24: J124.1, U$625.P3
GPIO0/SYNC25: J129.1, U$651.P3
GPIO0/SYNC26: J134.1, U$677.P3
GPIO0/SYNC27: J139.1, U$703.P3
GPIO0/SYNC28: J144.1, U$729.P3
GPIO0/SYNC29: J149.1, U$755.P3
GPIO0/SYNC30: J154.1, U$781.P3
GPIO0/SYNC31: J159.1, U$807.P3
GPIO0/SYNC32: J164.1, U$833.P3
GPIO0/SYNC33: J169.1, U$859.P3
GPIO0/SYNC34: J174.1, U$885.P3
GPIO0/SYNC35: J179.1, U$911.P3
GPIO0/SYNC36: J184.1, U$937.P3
GPIO0/SYNC37: J189.1, U$963.P3
GPIO0/SYNC38: J194.1, U$989.P3
GPIO0/SYNC39: J199.1, U$1015.P3
GPIO0/SYNC40: J204.1, U$1041.P3
GPIO0/SYNC41: J209.1, U$1067.P3
GPIO0/SYNC42: J214.1, U$1093.P3
GPIO0/SYNC43: J219.1, U$1119.P3
GPIO0/SYNC44: J224.1, U$1145.P3
GPIO0/SYNC45: J229.1, U$1171.P3
GPIO0/SYNC46: J234.1, U$1197.P3
GPIO0/SYNC47: J239.1, U$1223.P3
GPIO0/SYNC48: J244.1, U$1249.P3
GPIO0/SYNC49: J249.1, U$1275.P3
GPIO0/SYNC50: J254.1, U$1301.P3
GPIO0/SYNC51: J259.1, U$1327.P3
GPIO0/SYNC52: J264.1, U$1353.P3
GPIO0/SYNC53: J269.1, U$1379.P3
GPIO1: J3.2, U$1.P10
GPIO2: J10.2, U$17.P10
GPIO3: J15.2, U$53.P10
GPIO4: J20.2, U$79.P10
GPIO5: J25.2, U$105.P10
GPIO6: J30.2, U$131.P10
GPIO7: J35.2, U$157.P10
GPIO8: J40.2, U$183.P10
GPIO9: J45.2, U$209.P10
GPIO10: J50.2, U$235.P10
GPIO11: J55.2, U$261.P10
GPIO12: J60.2, U$287.P10
GPIO13: J65.2, U$313.P10
GPIO14: J70.2, U$339.P10
GPIO15: J75.2, U$365.P10
GPIO16: J80.2, U$391.P10
GPIO17: J85.2, U$417.P10
GPIO18: J90.2, U$443.P10
GPIO19: J95.2, U$469.P10
GPIO20: J100.2, U$495.P10
GPIO21: J105.2, U$521.P10
GPIO22: J110.2, U$547.P10
GPIO23: J115.2, U$573.P10
GPIO24: J120.2, U$599.P10
GPIO25: J125.2, U$625.P10
GPIO26: J130.2, U$651.P10
GPIO27: J135.2, U$677.P10
GPIO28: J140.2, U$703.P10
GPIO29: J145.2, U$729.P10
GPIO30: J150.2, U$755.P10
GPIO31: J155.2, U$781.P10
GPIO32: J160.2, U$807.P10
GPIO33: J165.2, U$833.P10
GPIO34: J170.2, U$859.P10
GPIO35: J175.2, U$885.P10
GPIO36: J180.2, U$911.P10
GPIO37: J185.2, U$937.P10
GPIO38: J190.2, U$963.P10
GPIO39: J195.2, U$989.P10
GPIO40: J200.2, U$1015.P10
GPIO41: J205.2, U$1041.P10
GPIO42: J210.2, U$1067.P10
GPIO43: J215.2, U$1093.P10
GPIO44: J220.2, U$1119.P10
GPIO45: J225.2, U$1145.P10
GPIO46: J230.2, U$1171.P10
GPIO47: J235.2, U$1197.P10
GPIO48: J240.2, U$1223.P10
GPIO49: J245.2, U$1249.P10
GPIO50: J250.2, U$1275.P10
GPIO51: J255.2, U$1301.P10
GPIO52: J260.2, U$1327.P10
GPIO53: J265.2, U$1353.P10
GPIO54: J270.2, U$1379.P10
unnamed: D1.A, R8.1
unnamed: LED1.1, R8.2
unnamed: I2C1.3, R4.2
unnamed: I2C1.1, R7.2
unnamed: D2.A, R6.1
unnamed: LED.1, R6.2
unnamed: I2C.3, R3.2
unnamed: I2C.1, R5.2
unnamed: D3.A, R13.1
unnamed: LED2.1, R13.2
unnamed: I2C2.3, R11.2
unnamed: I2C2.1, R12.2
unnamed: D4.A, R18.1
unnamed: LED3.1, R18.2
unnamed: I2C3.3, R16.2
unnamed: I2C3.1, R17.2
unnamed: D5.A, R23.1
unnamed: LED4.1, R23.2
unnamed: I2C4.3, R21.2
unnamed: I2C4.1, R22.2
unnamed: D6.A, R28.1
unnamed: LED5.1, R28.2
unnamed: I2C5.3, R26.2
unnamed: I2C5.1, R27.2
unnamed: D7.A, R33.1
unnamed: LED6.1, R33.2
unnamed: I2C6.3, R31.2
unnamed: I2C6.1, R32.2
unnamed: D8.A, R38.1
unnamed: LED7.1, R38.2
unnamed: I2C7.3, R36.2
unnamed: I2C7.1, R37.2
unnamed: D9.A, R43.1
unnamed: LED8.1, R43.2
unnamed: I2C8.3, R41.2
unnamed: I2C8.1, R42.2
unnamed: D10.A, R48.1
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
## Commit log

2021-12-02 Adds an additional folder for second part
2021-12-03 Routes entire board - rough draft
2021-12-06 Adds silk to TMF8820, updates footprint with pin 1 indicator
2021-12-06 Moves correct TMF8820 files into the correct folder
2021-12-06 Copies 8820 and overwrites 8821 design files (no silk changes yet)
2021-12-06 Adds "TMF8821" silk to the 8821 board design files
    * Replaces device with TMF8821 in schematic and updates text
2021-12-06 Adds VCC Range to schematic in both designs
2021-12-06 Adds two more designs - the "half qwiic" size boards (it's what it sounds like)
2021-12-06 Adds datasheets
2021-12-07 Adds default address to HQ boards, fixes some clearance issues
2021-12-08 Moves header to one side on the 1"x1" Qwiic Board
2021-12-08 Updates the TMF882X device in the library to have two variants of the two ICs
    * Better silk labeling for the 8820 and 8820 HQ
    * Adds new IC variants to both designs
    * Adds default addresses to schematics
    * Moves some traces and vias for better ground pour in the 8820 design
    * Moves entire 8820 design to origin in board file
    * Adds measure from center of qwiic connector to edge in 8820 design
2021-12-08 Copies 8820 designs to create 8821 designs - updates relevant references to 8820 to 8821
2021-12-08 Approves some overlap errors on jumpers and ground wire "stub"
2021-12-08 Adds logos to schematic
    * Moves measures to board (weren't moved when the design was put at the origin)
    * Replaces IO1 silk with IO0 on GPIO0 PTH header
2021-12-09 Rotates "IO0" silk on bottom side of regular Qwiic versions of the product
2021-12-09 Adds a two solder jumper for identifying whether the product has
    the 8820 or 8821 - to the 8820 Qwiic Board
2021-12-09 Adds gerbers for prototypes
2022-02-21 Moves IC to one side and all parts to the other
2022-02-22 Moves the IC on the SparkFun "HQ" design to one side
    * All other parts are on the other side. This makes room for product selection boxes so that one PCB can be used for both.
2022-02-22 Renames "HQ" files to "mini" to be consistent with new naming scheme
2022-02-22 Removes old production files
    * Removes old 8821 "HQ" variants
    * Copies the 8820 and 8820 Mini variants
    * Adjusts new 8820 copies to reference 8821 and replaces 8820 with 8821
    * Updates Product Identifier jumpers to reflect changes
2022-02-23 Adds new product identifier pads to all designs, rolls 8820 version number to v10
2022-02-23 Changes all "IO" silk to be "GP" instead, increases Qwiic pill size on mini's
    * Fixes orientation of I2C and LED silk on mini versions
    * Increases SparkFun flame size on mini versions
2022-02-23 Adds OSHW logo to boards, fixes silk width of new product identifier pads
2022-02-24 Adds production files for all products
    * The 8821 and 8821 Mini do not have their own PCBs
    * However they do have their own paste layers which I've included in the Production Files
2022-02-25 Fixes Sync silk on GP1 through hole on Qwiic sized designs
2022-02-25 Adds new panel with corrected silk
2022-04-07 Update File Names
    There was a minor typo in the file names. Changing all file names: tDoF => dToF
2022-04-07 Move to Hardware folder
    Move design files into Hardware folder
2022-04-20 Removes library used for prototyping - sensor has been moved to main SparkFun Eagle Library
2023-10-23 Adds license
